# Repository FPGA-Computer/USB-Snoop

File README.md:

USB-Snoop A low cost hardware dongle for capturing and analyzing Full Speed (12Mbps) traffic using ARM microcontroller

Project detail: https://hackaday.io/project/20532-usb-packet-snooping

Firmware/ - dongle firmware - Keil MDK

Hardware/ - Eagle CAD schematic, PCB, Sketchup 3D model (zipped)

Windows Software/ - Pellec C

All of software, firmware written by me are licensed under GPL 3.0. Additional incorporated open sourced code are under their own licenses.

Hardware is licensed under CC BY-4.0

https://creativecommons.org/licenses/by/4.0/

Compilers:

Pelles C compiler (freeware): http://www.smorgasbordet.com/pellesc/

Keil's free-to-use professional tool suite - MDK for STM32L0 and STM32F0 http://www2.keil.com/stmicroelectronics-stm32/mdk

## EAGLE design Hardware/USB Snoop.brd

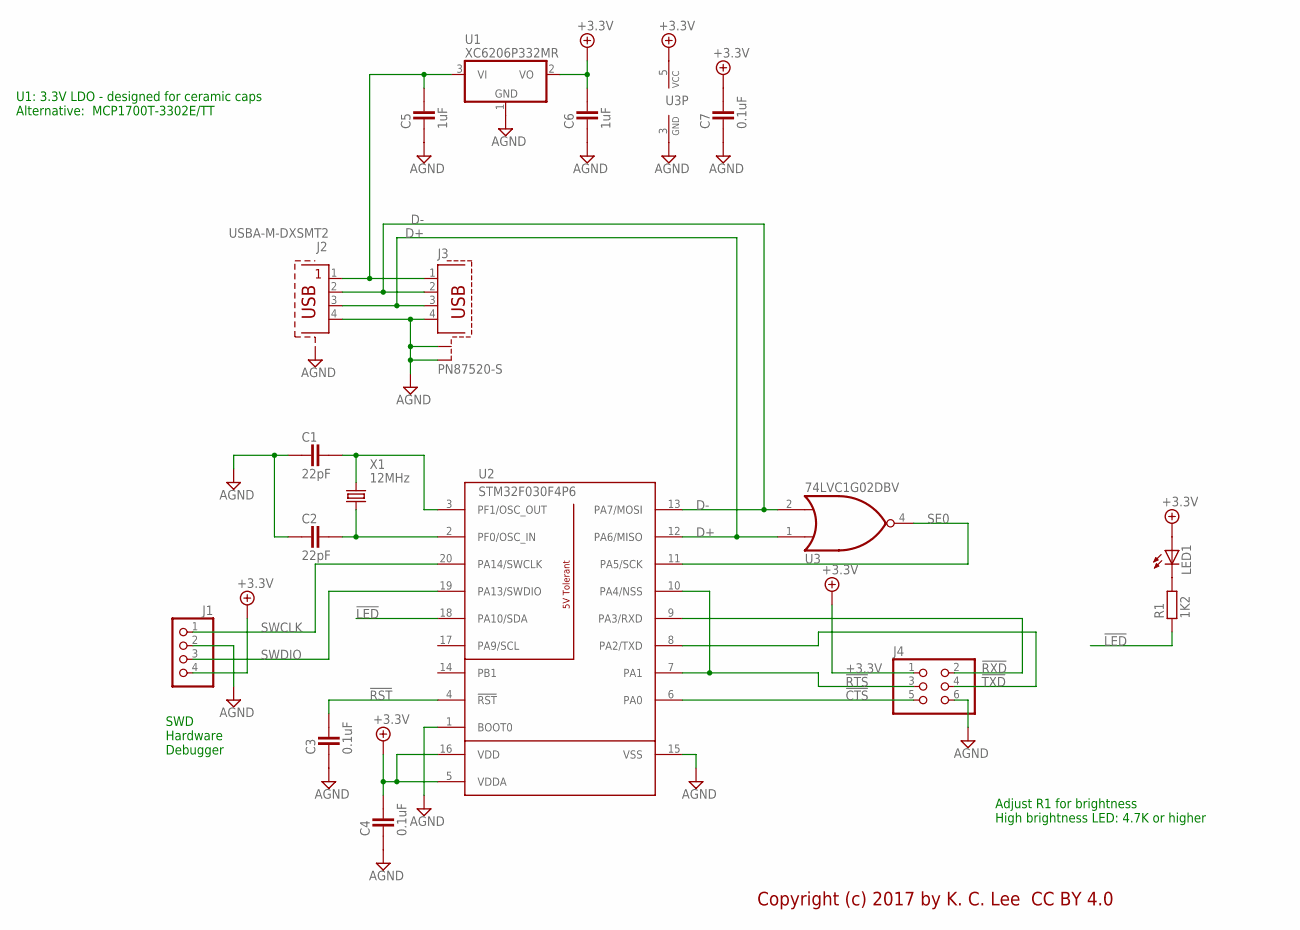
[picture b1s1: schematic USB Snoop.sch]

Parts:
C1, C2: 22pF; CAPC1608X92N; PARTNO *
C3, C4, C7: 0.1uF; CAPC1608X92N; PARTNO *
C5, C6: 1uF; CAPC1608X92N; PARTNO STOCK: 1UF/10V 20% TDK
J1: PINHD-1X4_2.54; 1X04; PARTNO 1X04 HEADER 2.54MM
J2: USBA-M-DXSMT2; CHINESE_USB_M_SMT-2; PARTNO *
J3: PN87520-S; PARTNO *
J4: PINHD-2X3_2.00; 2X03M_TH; PARTNO *
LED1: LEDSML0603; SML0603; PARTNO *
R1: 1K2; RESC1608X55N; PARTNO *
U1: XC6206P332MR; SOT95P280X135-3N; PARTNO *
U2: STM32F030F4P6; TSSOP20; PARTNO *
U3: 74LVC1G02DBV; SOT23-5; PARTNO *
X1: 12MHz; TC26H; PARTNO *

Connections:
!CTS: J4.5, U2.6 (PA0)
!LED: R1.1, U2.18 (PA10/SDA)
!RST: C3.2, U2.4 (!RST)
!RTS: J4.3, U2.7 (PA1), U2.10 (PA4/NSS)
!RXD: J4.2, U2.9 (PA3/RXD)
!TXD: J4.4, U2.8 (PA2/TXD)
+3.3V: C4.2, C6.2, C7.2, J1.4, J4.1, LED1.A, U1.2 (VO), U2.5 (VDDA), U2.16 (VDD), U3.5 (VCC)
AGND: C1.1, C2.1, C3.1, C4.1, C5.1, C6.1, C7.1, J1.2, J2.4, J2.S1, J2.S2 (S1), J3.4, J3.S1, J3.S2, J4.6, U1.1 (GND), U2.1 (BOOT0), U2.15 (VSS), U3.3 (GND)
D+: J2.3, J3.3, U2.12 (PA6/MISO), U3.1 (I0)
D-: J2.2, J3.2, U2.13 (PA7/MOSI), U3.2 (I1)
unnamed: C2.2, U2.2 (PF0/OSC_IN), X1.2
unnamed: LED1.C, R1.2
unnamed: C1.2, U2.3 (PF1/OSC_OUT), X1.1
SE0: U2.11 (PA5/SCK), U3.4 (O)
SWCLK: J1.1, U2.20 (PA14/SWCLK)
SWDIO: J1.3, U2.19 (PA13/SWDIO)
VUSB: C5.2, J2.1, J3.1, U1.3 (VI)

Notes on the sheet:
SWD Hardware Debugger
Copyright (c) 2017 by K. C. Lee CC BY 4.0
U1: 3.3V LDO - designed for ceramic caps Alternative: MCP1700T-3302E/TT
Adjust R1 for brightness High brightness LED: 4.7K or higher

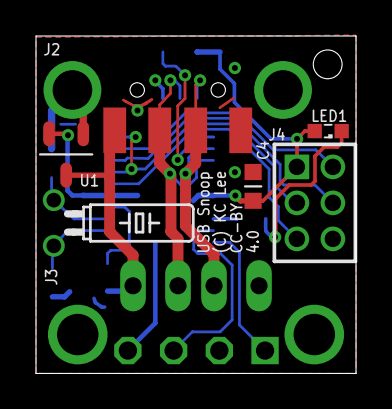
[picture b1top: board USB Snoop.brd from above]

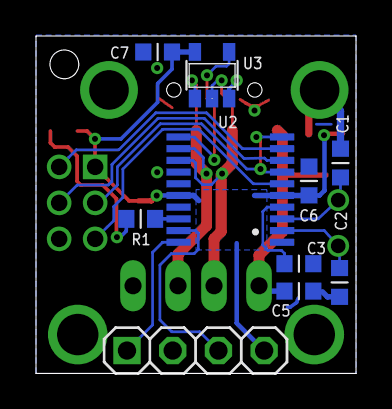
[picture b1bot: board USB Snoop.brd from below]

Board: 2 copper layers, 17.8 x 18.7 mm, 17 parts (10 on the bottom side), 17 nets.

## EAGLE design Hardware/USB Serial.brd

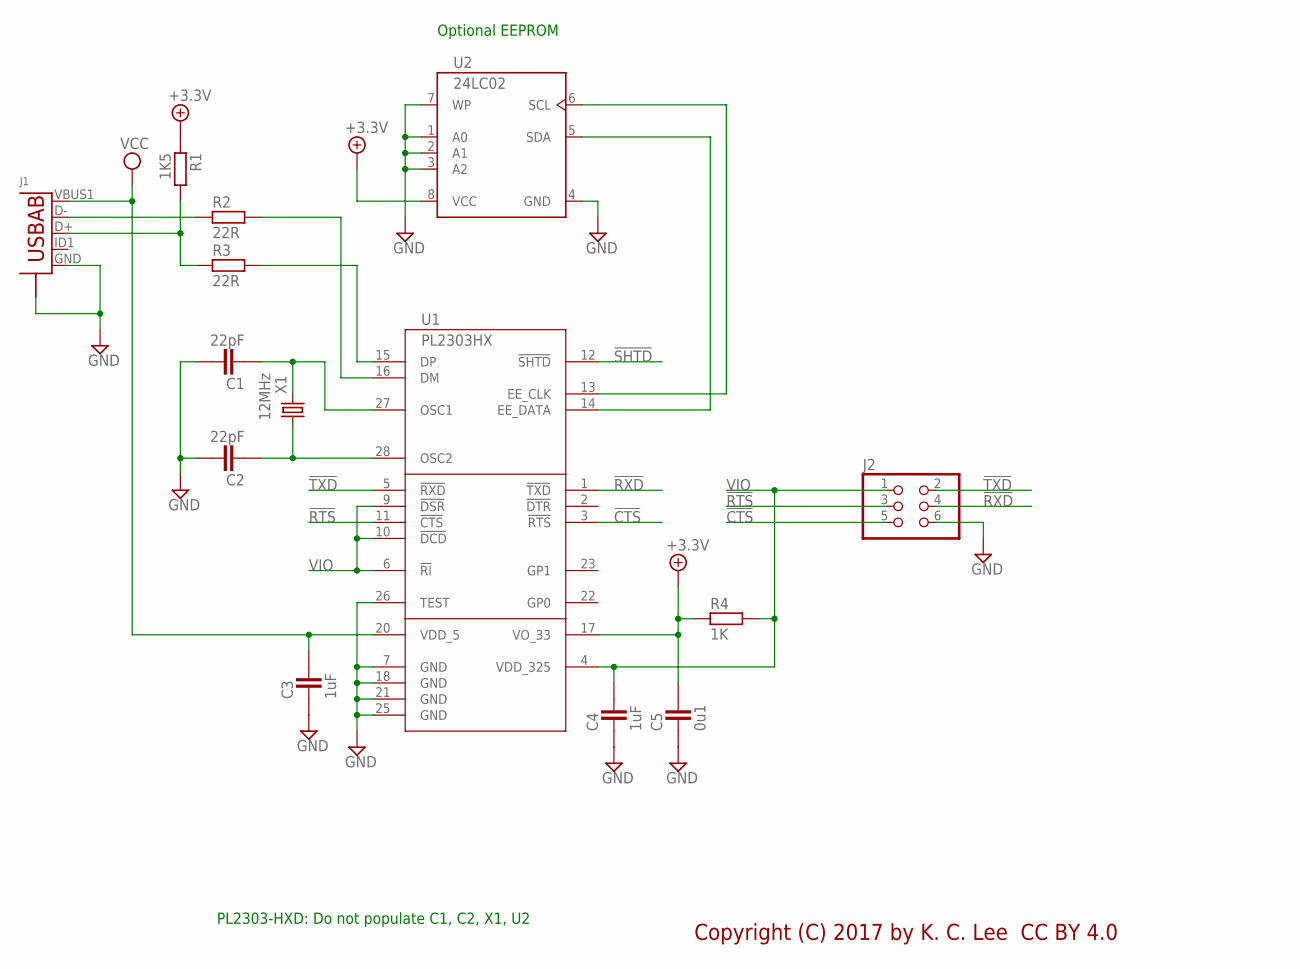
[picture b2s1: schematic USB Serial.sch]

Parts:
C1, C2: 22pF; CAPC1608X92N; PARTNO 22PF 0603
C3, C4: 1uF; CAPC1608X92N; PARTNO 1UF X7R 0603
C5: 0u1; CAPC1608X92N; PARTNO 0U1 X7R 0603
J1: USB-ABBG-ORG; USB-AB-MICRO-SMD_V03_SMT; PARTNO SMT MICRO USB FEMALE
J2: PINHD-2X3_2.00; 2X03M_TH; PARTNO 3X2 HEADER 2MM THROUGH HOLE
R1: 1K5; RESC1608X55N; PARTNO 1K5 0603
R2, R3: 22R; RESC1608X55N; PARTNO 22R 0603
R4: 1K; RESC1608X55N; PARTNO 1K 0603
U1: PL2303HX; SSOP28DB; PARTNO PL-2303HXD SSOP
U2: 24LC02; TSSOP8; PARTNO 24LC02
X1: 12MHz; TC26H; PARTNO 12MHZ TC26

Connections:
!CTS: J2.5, U1.3 (!RTS)
!RTS: J2.3, U1.11 (!CTS)
!RXD: J2.4, U1.1 (!TXD)
!SHTD: U1.12 (!SHTD)
!TXD: J2.2, U1.5 (!RXD)
+3.3V: C5.2, R1.1, R4.1, U1.17 (VO_33), U2.8 (VCC)
GND: C1.2, C2.2, C3.1, C4.1, C5.1, J1.GND, J1.S1 (S), J1.S2 (S), J1.S3 (S), J1.S4 (S), J2.6, U1.7 (GND), U1.18 (GND), U1.21 (GND), U1.25 (GND), U1.26 (TEST), U2.1 (A0), U2.2 (A1), U2.3 (A2), U2.4 (GND), U2.7 (WP)
unnamed: R3.2, U1.15 (DP)
unnamed: J1.D+, R1.2, R3.1
unnamed: J1.D-, R2.1
unnamed: R2.2, U1.16 (DM)
unnamed: U1.14 (EE_DATA), U2.5 (SDA)
unnamed: U1.13 (EE_CLK), U2.6 (SCL)
unnamed: C1.1, U1.27 (OSC1), X1.2
unnamed: C2.1, U1.28 (OSC2), X1.1
VCC: C3.2, J1.VBUS1 (VBUS), U1.20 (VDD_5)
VIO: C4.2, J2.1, R4.2, U1.4 (VDD_325), U1.6 (!RI), U1.9 (!DSR), U1.10 (!DCD)

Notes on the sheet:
Copyright (C) 2017 by K. C. Lee CC BY 4.0
Optional EEPROM
PL2303-HXD: Do not populate C1, C2, X1, U2

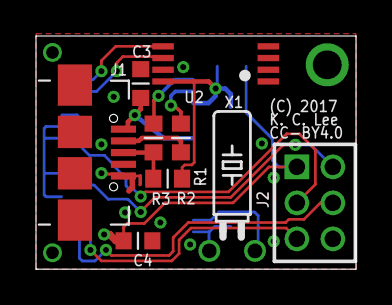
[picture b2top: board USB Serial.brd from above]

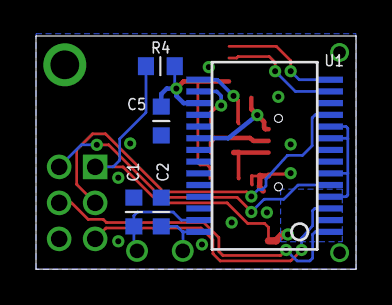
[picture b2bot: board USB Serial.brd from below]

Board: 2 copper layers, 17.8 x 13.0 mm, 14 parts (5 on the bottom side), 16 nets.

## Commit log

2017-04-28 Initial commit - hardware untested
2017-04-28 Update README.md
    Formatting
2017-04-29 Minor fix up on BOM
2017-05-03 Update PCB BOM
